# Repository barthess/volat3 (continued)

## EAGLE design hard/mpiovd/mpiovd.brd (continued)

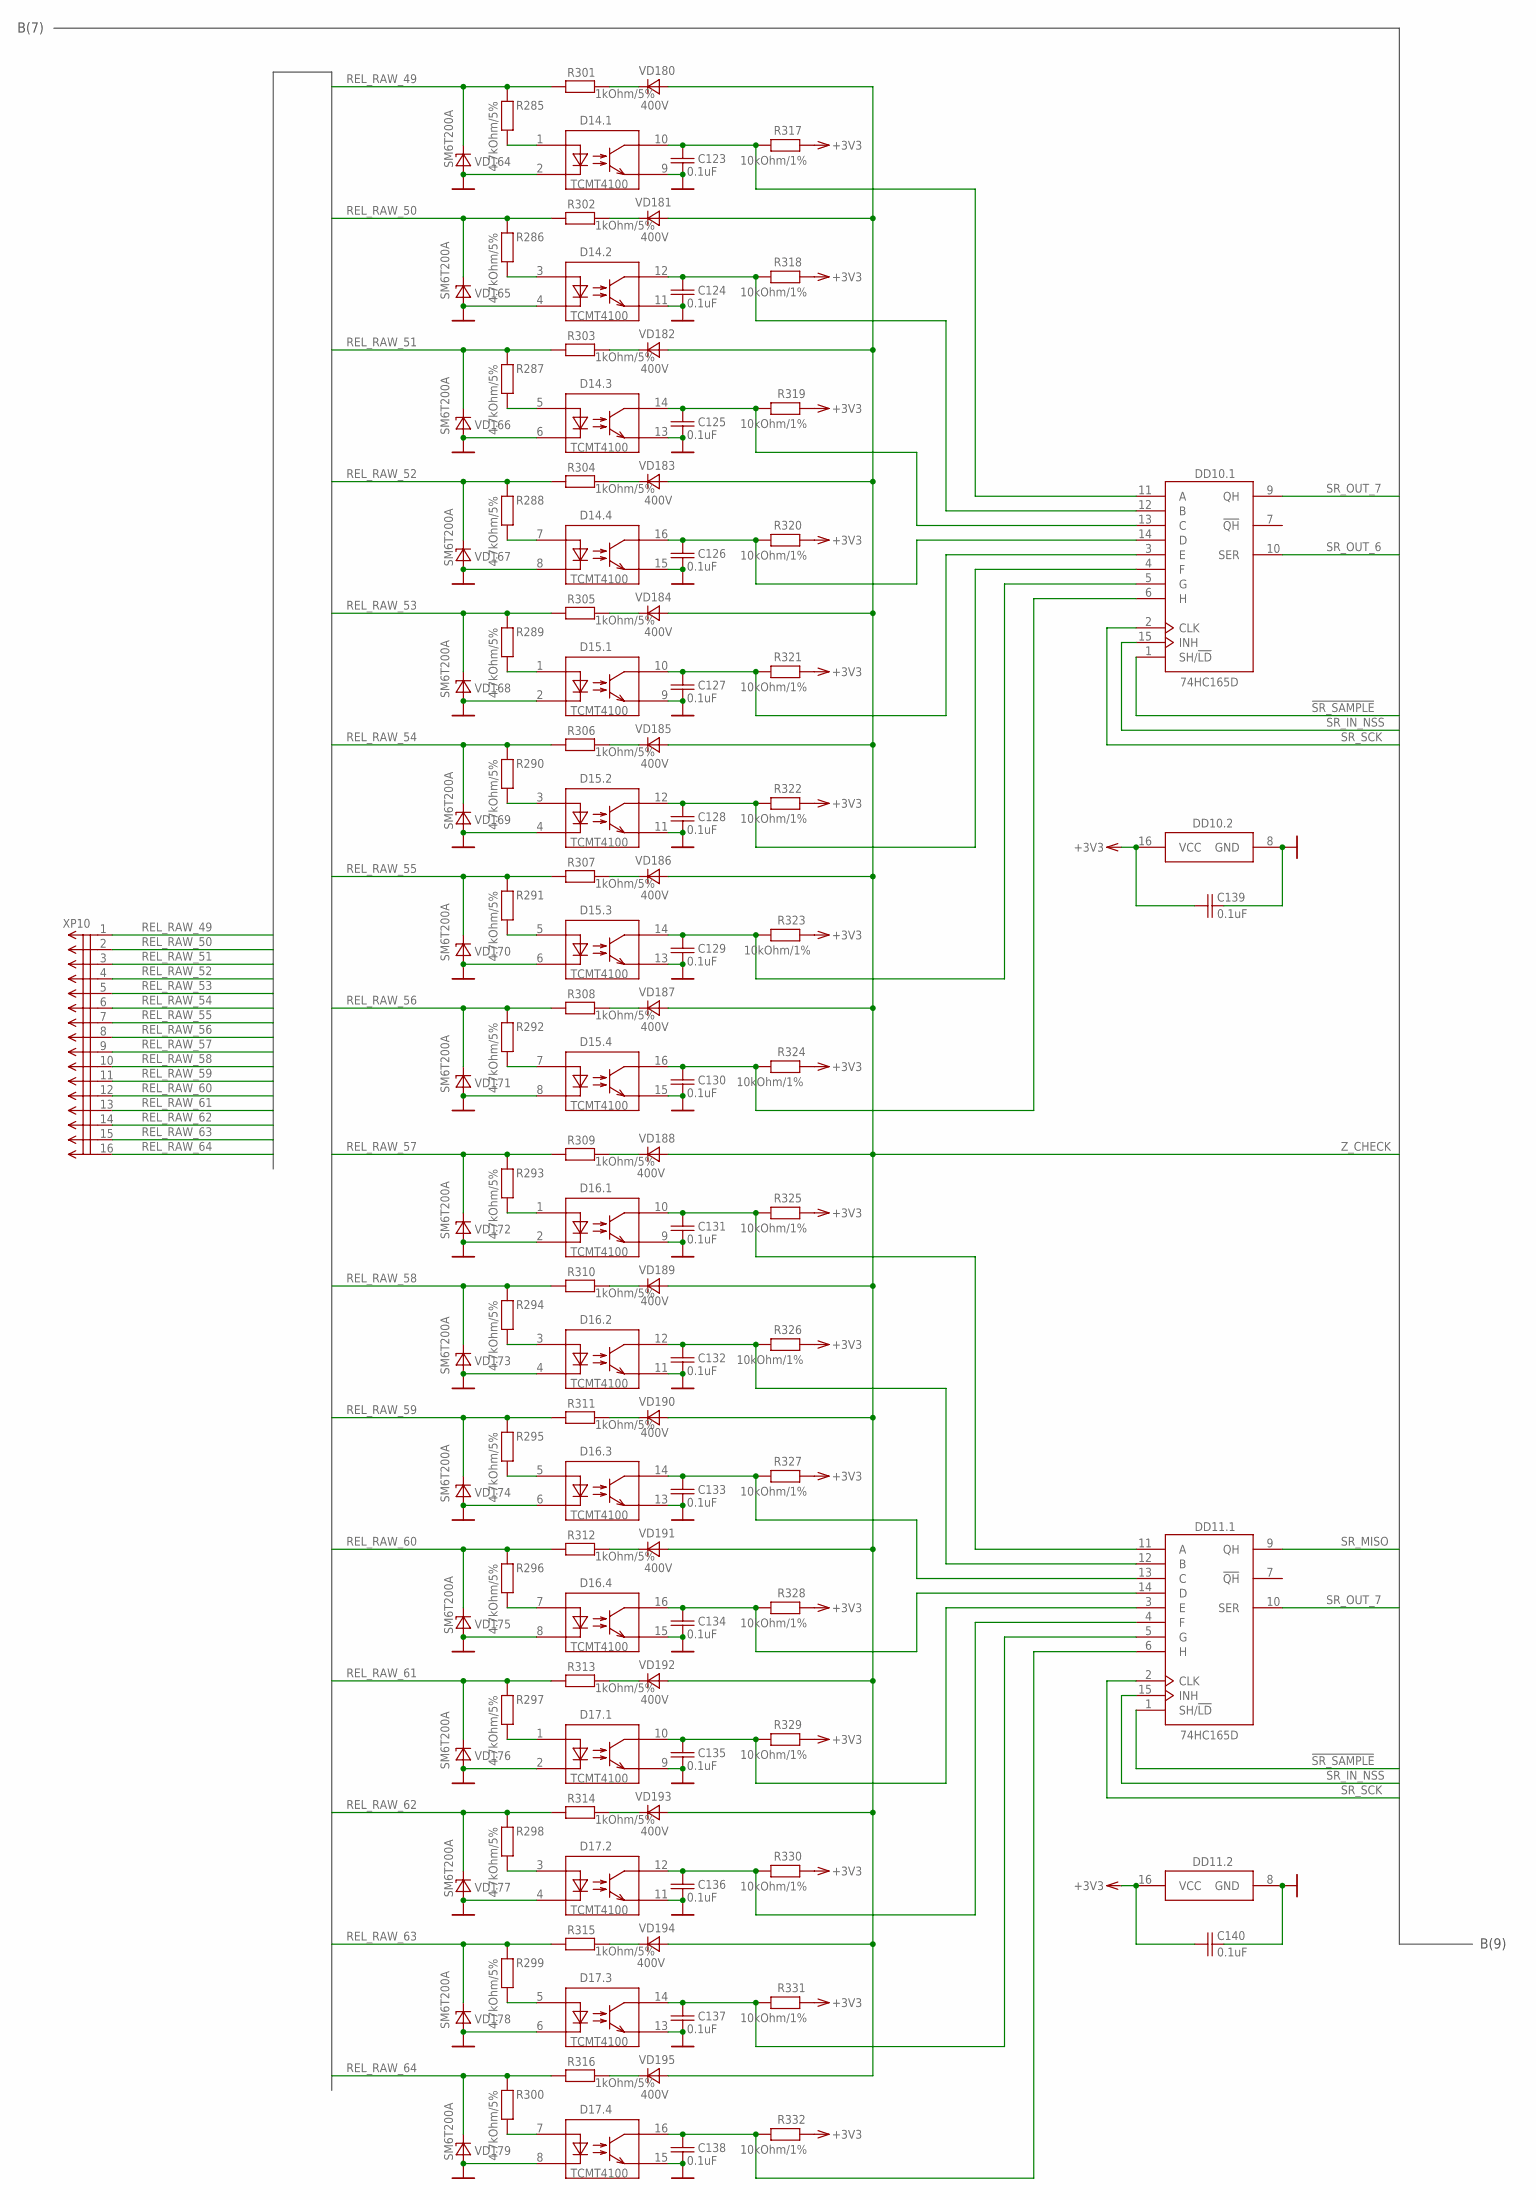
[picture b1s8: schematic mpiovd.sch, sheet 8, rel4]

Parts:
C123, C124, C125, C126, C127, C128, C129, C130, C131, C132, C133, C134, C135, C136, C137, C138, C139, C140: 0.1uF; C0603; PARTNO C0603C104K5RACTU
D14, D15, D16, D17: TCMT4100; SO16; PARTNO TCMT4100
DD10, DD11: 74HC165D; SO16; PARTNO IN74HC165AD
R285, R286, R287, R288, R289, R290, R291, R292, R293, R294, R295, R296, R297, R298, R299, R300: 4.7kOhm/5%; R1206; PARTNO RC1206JR-074K7L
R301, R302, R303, R304, R305, R306, R307, R308, R309, R310, R311, R312, R313, R314, R315, R316: 1kOhm/5%; R2512; PARTNO RC2512JK-071KL
R317, R318, R319, R320, R321, R322, R323, R324, R325, R326, R327, R328, R329, R330, R331, R332: 10kOhm/1%; R0603; PARTNO RC0603FR-1010KL
VD164, VD165, VD166, VD167, VD168, VD169, VD170, VD171, VD172, VD173, VD174, VD175, VD176, VD177, VD178, VD179: SM6T200A; SMB; PARTNO SM6T200A
VD180, VD181, VD182, VD183, VD184, VD185, VD186, VD187, VD188, VD189, VD190, VD191, VD192, VD193, VD194, VD195: 400V; SMA; PARTNO S1G-E3/61T
XP10: MOLEX-90130-16; PARTNO 90130-1216

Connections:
!SR_SAMPLE: DD10.1 (SH/!LD), DD11.1 (SH/!LD); also elsewhere on the board
+3V3: C139.1, C140.1, DD10.16 (VCC), DD11.16 (VCC), R317.1, R318.1, R319.1, R320.1, R321.1, R322.1, R323.1, R324.1, R325.1, R326.1, R327.1, R328.1, R329.1, R330.1, R331.1, R332.1; also elsewhere on the board
DISCRETE_49: C123.1, D14.10 (TC), DD10.11 (A), R317.2
DISCRETE_50: C124.1, D14.12 (TC), DD10.12 (B), R318.2
DISCRETE_51: C125.1, D14.14 (TC), DD10.13 (C), R319.2
DISCRETE_52: C126.1, D14.16 (TC), DD10.14 (D), R320.2
DISCRETE_53: C127.1, D15.10 (TC), DD10.3 (E), R321.2
DISCRETE_54: C128.1, D15.12 (TC), DD10.4 (F), R322.2
DISCRETE_55: C129.1, D15.14 (TC), DD10.5 (G), R323.2
DISCRETE_56: C130.1, D15.16 (TC), DD10.6 (H), R324.2
DISCRETE_57: C131.1, D16.10 (TC), DD11.11 (A), R325.2
DISCRETE_58: C132.1, D16.12 (TC), DD11.12 (B), R326.2
DISCRETE_59: C133.1, D16.14 (TC), DD11.13 (C), R327.2
DISCRETE_60: C134.1, D16.16 (TC), DD11.14 (D), R328.2
DISCRETE_61: C135.1, D17.10 (TC), DD11.3 (E), R329.2
DISCRETE_62: C136.1, D17.12 (TC), DD11.4 (F), R330.2
DISCRETE_63: C137.1, D17.14 (TC), DD11.5 (G), R331.2
DISCRETE_64: C138.1, D17.16 (TC), DD11.6 (H), R332.2
GND: C123.2, C124.2, C125.2, C126.2, C127.2, C128.2, C129.2, C130.2, C131.2, C132.2, C133.2, C134.2, C135.2, C136.2, C137.2, C138.2, C139.2, C140.2, D14.2 (DC), D14.4 (DC), D14.6 (DC), D14.8 (DC), D14.9 (TE), D14.11 (TE), D14.13 (TE), D14.15 (TE), D15.2 (DC), D15.4 (DC), D15.6 (DC), D15.8 (DC), D15.9 (TE), D15.11 (TE), D15.13 (TE), D15.15 (TE), D16.2 (DC), D16.4 (DC), D16.6 (DC), D16.8 (DC), D16.9 (TE), D16.11 (TE), D16.13 (TE), D16.15 (TE), D17.2 (DC), D17.4 (DC), D17.6 (DC), D17.8 (DC), D17.9 (TE), D17.11 (TE), D17.13 (TE), D17.15 (TE), DD10.8 (GND), DD11.8 (GND), VD164.A, VD165.A, VD166.A, VD167.A, VD168.A, VD169.A, VD170.A, VD171.A, VD172.A, VD173.A, VD174.A, VD175.A, VD176.A, VD177.A, VD178.A, VD179.A; also elsewhere on the board
unnamed: R301.2, VD180.C
unnamed: R302.2, VD181.C
unnamed: R303.2, VD182.C
unnamed: R304.2, VD183.C
unnamed: R305.2, VD184.C
unnamed: R306.2, VD185.C
unnamed: R307.2, VD186.C
unnamed: R308.2, VD187.C
unnamed: R309.2, VD188.C
unnamed: R310.2, VD189.C
unnamed: R311.2, VD190.C
unnamed: R312.2, VD191.C
unnamed: R313.2, VD192.C
unnamed: R314.2, VD193.C
unnamed: R315.2, VD194.C
unnamed: R316.2, VD195.C
unnamed: D14.1 (DA), R285.2
unnamed: D14.3 (DA), R286.2
unnamed: D14.5 (DA), R287.2
unnamed: D14.7 (DA), R288.2
unnamed: D15.1 (DA), R289.2
unnamed: D15.3 (DA), R290.2
unnamed: D15.5 (DA), R291.2
unnamed: D15.7 (DA), R292.2
unnamed: D16.1 (DA), R293.2
unnamed: D16.3 (DA), R294.2
unnamed: D16.5 (DA), R295.2
unnamed: D16.7 (DA), R296.2
unnamed: D17.1 (DA), R297.2
unnamed: D17.3 (DA), R298.2
unnamed: D17.5 (DA), R299.2
unnamed: D17.7 (DA), R300.2
REL_RAW_49: R285.1, R301.1, VD164.C, XP10.1
REL_RAW_50: R286.1, R302.1, VD165.C, XP10.2
REL_RAW_51: R287.1, R303.1, VD166.C, XP10.3
REL_RAW_52: R288.1, R304.1, VD167.C, XP10.4
REL_RAW_53: R289.1, R305.1, VD168.C, XP10.5
REL_RAW_54: R290.1, R306.1, VD169.C, XP10.6
REL_RAW_55: R291.1, R307.1, VD170.C, XP10.7
REL_RAW_56: R292.1, R308.1, VD171.C, XP10.8
REL_RAW_57: R293.1, R309.1, VD172.C, XP10.9
REL_RAW_58: R294.1, R310.1, VD173.C, XP10.10
REL_RAW_59: R295.1, R311.1, VD174.C, XP10.11
REL_RAW_60: R296.1, R312.1, VD175.C, XP10.12
REL_RAW_61: R297.1, R313.1, VD176.C, XP10.13
REL_RAW_62: R298.1, R314.1, VD177.C, XP10.14
REL_RAW_63: R299.1, R315.1, VD178.C, XP10.15
REL_RAW_64: R300.1, R316.1, VD179.C, XP10.16
SR_IN_NSS: DD10.15 (INH), DD11.15 (INH); also elsewhere on the board
SR_MISO: DD11.9 (QH); also elsewhere on the board
SR_OUT_6: DD10.10 (SER); also elsewhere on the board
SR_OUT_7: DD10.9 (QH), DD11.10 (SER)
SR_SCK: DD10.2 (CLK), DD11.2 (CLK); also elsewhere on the board
Z_CHECK: VD180.A, VD181.A, VD182.A, VD183.A, VD184.A, VD185.A, VD186.A, VD187.A, VD188.A, VD189.A, VD190.A, VD191.A, VD192.A, VD193.A, VD194.A, VD195.A; also elsewhere on the board

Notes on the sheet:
B(9)
B(7)

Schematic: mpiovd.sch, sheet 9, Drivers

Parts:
C141: 0.1uF; C0603; PARTNO C0603C104K5RACTU
D18, D19: TCMT4100; SO16; PARTNO TCMT4100
D20, D21, D22, D23, D24, D25, D26, D27: AUIPS7111S; TO252-5-11; PARTNO AUIPS7111S
DD12: 74HC595D; SO16; PARTNO IN74HC595AD
R333: 10kOhm/1%; R0603; PARTNO RC0603FR-1010KL
R334, R335, R336, R337, R338, R339, R340, R341: 100Ohm/5%; R0603; PARTNO ERJ3GEYJ101V
R342, R343, R344, R345, R346, R347, R348, R349, R350, R351, R352, R353, R354, R355, R356, R357: 1kOhm/5%; R0805; PARTNO ERJ6GEYJ102V
VD196, VD197, VD198, VD199, VD200, VD201, VD202, VD203, VD204, VD205, VD206, VD207, VD208, VD209, VD210, VD211: 100V; SOD323; PARTNO 1N4148WS-V-GS18
XP11: MOLEX-90130-34; PARTNO 90130-1234

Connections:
!SR_OUT_ENABLE: DD12.13 (!OE), R333.1; also elsewhere on the board
+3V3: C141.1, DD12.10 (!MR), DD12.16 (VCC), R333.2; also elsewhere on the board
GND: C141.2, D18.2 (DC), D18.4 (DC), D18.6 (DC), D18.8 (DC), D18.9 (TE), D18.11 (TE), D18.13 (TE), D18.15 (TE), D19.2 (DC), D19.4 (DC), D19.6 (DC), D19.8 (DC), D19.9 (TE), D19.11 (TE), D19.13 (TE), D19.15 (TE), DD12.8 (GND), R342.1, R343.1, R344.1, R345.1, R346.1, R347.1, R348.1, R349.1, VD196.A, VD197.A, VD198.A, VD199.A, VD200.A, VD201.A, VD202.A, VD203.A; also elsewhere on the board
unnamed: D27.1 (IN), R357.2
unnamed: D26.1 (IN), R356.2
unnamed: D25.1 (IN), R355.2
unnamed: D24.1 (IN), R354.2
unnamed: D23.1 (IN), R353.2
unnamed: D22.1 (IN), R352.2
unnamed: D21.1 (IN), R351.2
unnamed: D20.1 (IN), R350.2
unnamed: D19.7 (DA), R341.1
unnamed: D18.10 (TC), R350.1, VD196.C
unnamed: D18.12 (TC), R351.1, VD197.C
unnamed: D18.14 (TC), R352.1, VD198.C
unnamed: D18.16 (TC), R353.1, VD199.C
unnamed: D19.10 (TC), R354.1, VD200.C
unnamed: D19.12 (TC), R355.1, VD201.C
unnamed: D19.14 (TC), R356.1, VD202.C
unnamed: D19.16 (TC), R357.1, VD203.C
unnamed: D19.5 (DA), R340.1
unnamed: D19.3 (DA), R339.1
unnamed: D19.1 (DA), R338.1
unnamed: D18.7 (DA), R337.1
unnamed: D18.5 (DA), R336.1
unnamed: D18.3 (DA), R335.1
unnamed: D18.1 (DA), R334.1
unnamed: DD12.15 (QA), R334.2
unnamed: D20.2 (IFB), VD204.A
unnamed: D21.2 (IFB), VD205.A
unnamed: D22.2 (IFB), VD206.A
unnamed: D23.2 (IFB), VD207.A
unnamed: D24.2 (IFB), VD208.A
unnamed: D25.2 (IFB), VD209.A
unnamed: D26.2 (IFB), VD210.A
unnamed: D27.2 (IFB), VD211.A
unnamed: DD12.1 (QB), R335.2
unnamed: DD12.2 (QC), R336.2
unnamed: DD12.7 (QH), R341.2
unnamed: DD12.6 (QG), R340.2
unnamed: DD12.5 (QF), R339.2
unnamed: R342.2, VD204.C
unnamed: R343.2, VD205.C
unnamed: R344.2, VD206.C
unnamed: R345.2, VD207.C
unnamed: R346.2, VD208.C
unnamed: DD12.3 (QD), R337.2
unnamed: DD12.4 (QE), R338.2
unnamed: R347.2, VD209.C
unnamed: R348.2, VD210.C
unnamed: R349.2, VD211.C
OUT_DRV1: D20.4 (OUT1), D20.5 (OUT2), XP11.1, XP11.4
OUT_DRV2: D21.4 (OUT1), D21.5 (OUT2), XP11.5, XP11.8
OUT_DRV3: D22.4 (OUT1), D22.5 (OUT2), XP11.9, XP11.12
OUT_DRV4: D23.4 (OUT1), D23.5 (OUT2), XP11.13, XP11.16
OUT_DRV5: D24.4 (OUT1), D24.5 (OUT2), XP11.17, XP11.20
OUT_DRV6: D25.4 (OUT1), D25.5 (OUT2), XP11.21, XP11.24
OUT_DRV7: D26.4 (OUT1), D26.5 (OUT2), XP11.25, XP11.28
OUT_DRV8: D27.4 (OUT1), D27.5 (OUT2), XP11.29, XP11.32
SR_MOSI: DD12.14 (SER); also elsewhere on the board
SR_OUT_NSS: DD12.12 (STCP); also elsewhere on the board
SR_SCK: DD12.11 (SHCP); also elsewhere on the board
VCC_DRV1: D20.TAB (VCC), XP11.2, XP11.3
VCC_DRV2: D21.TAB (VCC), XP11.6, XP11.7
VCC_DRV3: D22.TAB (VCC), XP11.10, XP11.11
VCC_DRV4: D23.TAB (VCC), XP11.14, XP11.15
VCC_DRV5: D24.TAB (VCC), XP11.18, XP11.19
VCC_DRV6: D25.TAB (VCC), XP11.22, XP11.23
VCC_DRV7: D26.TAB (VCC), XP11.26, XP11.27
VCC_DRV8: D27.TAB (VCC), XP11.30, XP11.31

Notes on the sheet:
B(8)

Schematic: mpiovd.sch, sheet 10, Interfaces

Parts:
C142, C143, C144, C145, C146, C147: 0.1uF; C0603; PARTNO C0603C104K5RACTU
DA15: USBUF01W6; SOTT323-6L; PARTNO USBUF01W6
DA16: SN65HVD232; SO08; PARTNO SN65HVD232D
DA17: ILX3232D; SO16; PARTNO ILX3232D
L4: EXC3BP; L0603; PARTNO EXC3BP121H
R358: 120Ohm/5%; R1206; PARTNO RC1206JR-07120RL
R359, R361: 10kOhm/1%; R0603; PARTNO RC0603FR-1010KL
R360: 36kOhm/5%; R0603; PARTNO ERJ3GEYJ363V
R362: 47kOhm/5%; R0603; PARTNO ERJ3GEYJ473V
R363, R364: 1kOhm/5%; R0805; PARTNO ERJ6GEYJ102V
VD212, VD213: SMBJ24CA; SMB-BIDIR; PARTNO SMBJ24CA
VD214: 3.3V; SOD80; PARTNO BZV55-C3V3
VT3, VT4: BC817-16SMD; SOT23-BEC; PARTNO BC817
XP12: MOLEX-90130-08; PARTNO 90130-1208
XP13: PLD_1X02; PARTNO 825433-2
XS1: USB-MINIB_(SOVOK-UGO); USB-MINIB; PARTNO MUBS1-05SN2
Z42, Z43, Z44, Z45, Z46, Z47, Z48, Z49, Z50: NFE31PT; NFE31; PARTNO NFE31PT152Z1E9

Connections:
+3V3: C142.2, DA16.3 (VCC), R362.2, VT3.C; also elsewhere on the board
+3V3_DIRT: C144.1, DA17.16 (VCC); also elsewhere on the board
+5V_USB: L4.2, R359.2, R361.2, VT3.B; also elsewhere on the board
CANH: DA16.7 (CANH), XP12.2, XP13.1
CANL: DA16.6 (CANL), R358.2, XP12.1
CAN_RX: Z47.3; also elsewhere on the board
CAN_TX: Z50.3; also elsewhere on the board
D+: XS1.D+ (3), Z42.3
D-: XS1.D- (2), Z43.3
FROM_RS232: VD213.A2, XP12.3, Z46.1
GND: C142.1, C143.2, C144.2, C145.2, DA15.2 (GND), DA16.2 (GND), DA17.15 (GND), R360.1, VD212.A1, VD213.A1, VD214.A, VT4.E, XS1.GND (5), Z42.2, Z43.2, Z44.2, Z45.2, Z46.2, Z47.2, Z48.2, Z49.2, Z50.2; also elsewhere on the board
unnamed: R358.1, XP13.2
unnamed: R362.1, R364.1, VT4.B
unnamed: R359.1, R360.2, VT4.C
unnamed: VT3.E, Z44.3
unnamed: R361.1, R363.1, VD214.C
unnamed: L4.1, XS1.VBUS (1)
unnamed: C143.1, DA17.2 (V+)
unnamed: C145.1, DA17.6 (V-)
unnamed: DA17.8 (R2IN), Z46.3
unnamed: DA17.7 (T2OUT), Z45.3
unnamed: C146.2, DA17.3 (C1-)
unnamed: C146.1, DA17.1 (C1+)
unnamed: C147.1, DA17.4 (C2+)
unnamed: C147.2, DA17.5 (C2-)
unnamed: DA16.1 (TXD), Z50.1
unnamed: DA16.4 (RXD), Z47.1
unnamed: DA15.5 (3.3V), Z44.1
unnamed: R364.2, Z49.1
unnamed: R363.2, Z48.1
unnamed: DA15.4 (D3), Z43.1
unnamed: DA15.6 (D4), Z42.1
TO_RS232: VD212.A2, XP12.4, Z45.1
USART_FROM_MCU: DA17.10 (T2IN); also elsewhere on the board
USART_TO_MCU: DA17.9 (R2OUT); also elsewhere on the board
USBDM: DA15.3 (D2); also elsewhere on the board
USBDP: DA15.1 (D1); also elsewhere on the board
USB_DISCOVERY: Z49.3; also elsewhere on the board
USB_PRESENT: Z48.3; also elsewhere on the board

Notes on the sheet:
C(3)

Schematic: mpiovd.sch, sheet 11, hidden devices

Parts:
JP1, JP2, JP3, JP4, JP5, JP6, JP7, JP8: STAND-OFF-M4
JP9, JP10: STAND-OFF-M3

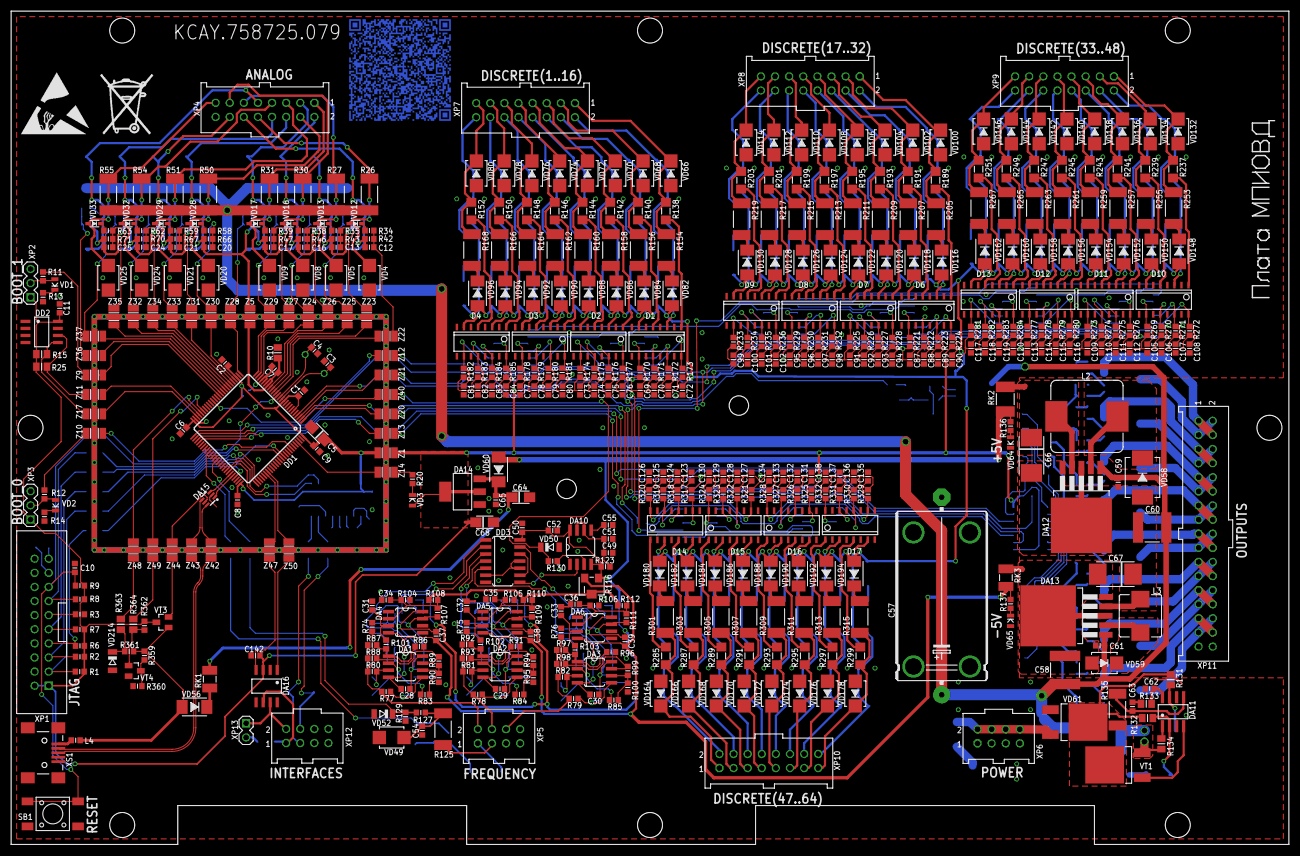
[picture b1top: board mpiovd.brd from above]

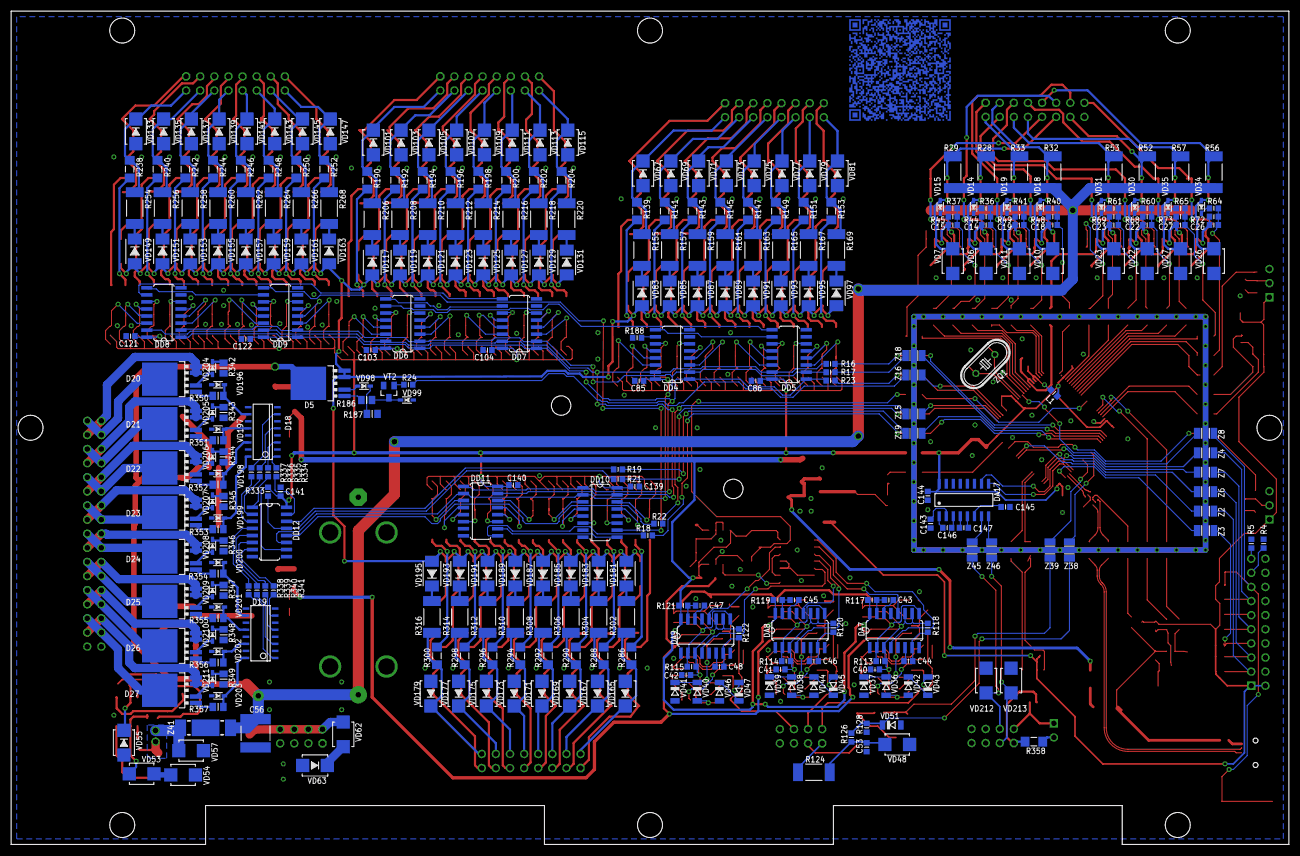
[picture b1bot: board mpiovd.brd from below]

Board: 2 copper layers, 230.0 x 150.0 mm, 871 parts (335 on the bottom side), 591 nets.

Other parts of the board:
U$1: STATIC_12
U$2: NOT_RECYCLE_12
U$3: QR

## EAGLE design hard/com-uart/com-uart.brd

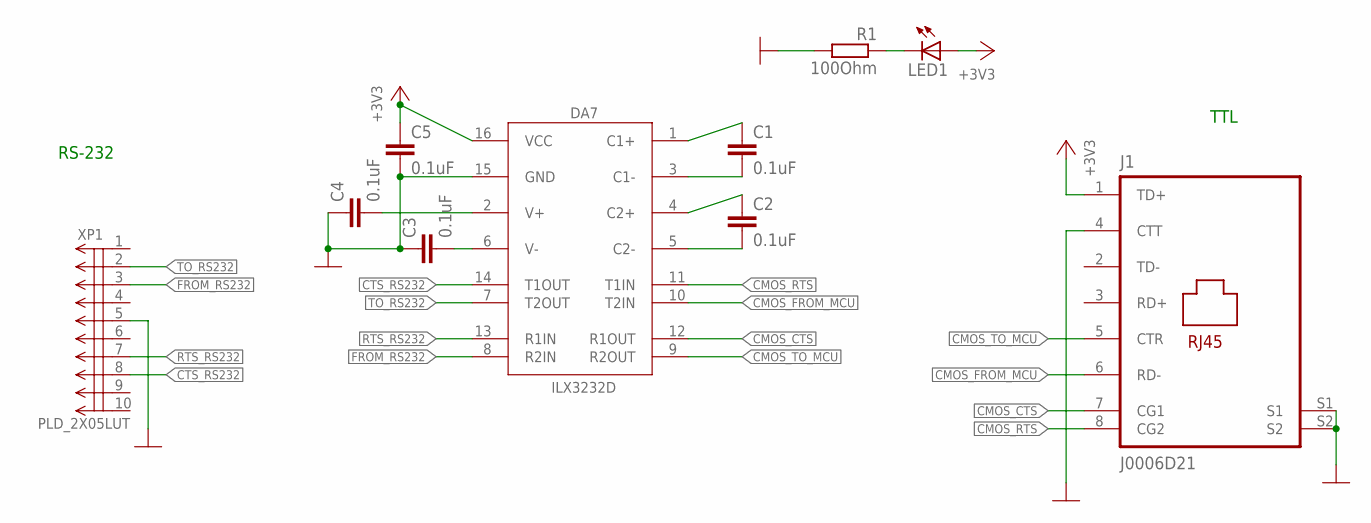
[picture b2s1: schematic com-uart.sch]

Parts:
C1, C2, C3, C4, C5: 0.1uF; 0805
DA7: ILX3232D; SO16; PARTNO ILX3232D
J1: J0006D21; J0-C/D/E
LED1: LED3MM
R1: 100Ohm; 0805
XP1: PLD_2X05LUT; PLD_2X05_LUT

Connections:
+3V3: C5.1, DA7.16 (VCC), J1.1 (TD+), LED1.A
CMOS_CTS: DA7.12 (R1OUT), J1.7 (CG1)
CMOS_FROM_MCU: DA7.10 (T2IN), J1.6 (RD-)
CMOS_RTS: DA7.11 (T1IN), J1.8 (CG2)
CMOS_TO_MCU: DA7.9 (R2OUT), J1.5 (CTR)
CTS_RS232: DA7.14 (T1OUT), XP1.8
FROM_RS232: DA7.8 (R2IN), XP1.3
GND: C3.1, C4.1, C5.2, DA7.15 (GND), J1.4 (CTT), J1.S1, J1.S2, R1.2, XP1.5
unnamed: LED1.K (C), R1.1
unnamed: C4.2, DA7.2 (V+)
unnamed: C3.2, DA7.6 (V-)
unnamed: C1.2, DA7.3 (C1-)
unnamed: C1.1, DA7.1 (C1+)
unnamed: C2.1, DA7.4 (C2+)
unnamed: C2.2, DA7.5 (C2-)
RTS_RS232: DA7.13 (R1IN), XP1.7
TO_RS232: DA7.7 (T2OUT), XP1.2

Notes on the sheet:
TTL
RS-232

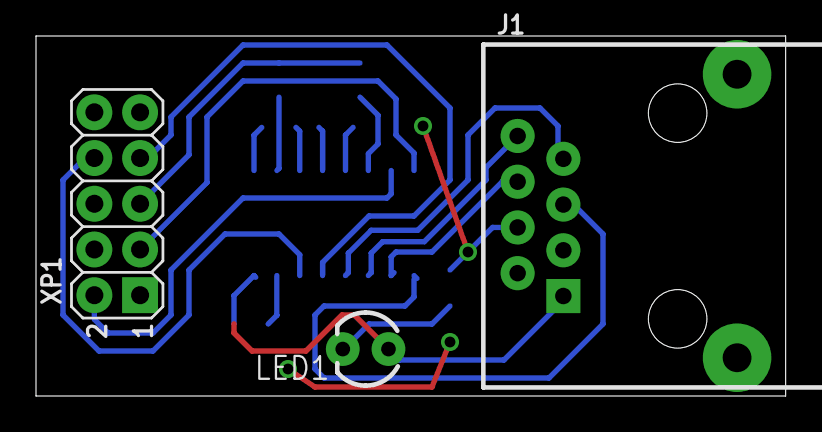
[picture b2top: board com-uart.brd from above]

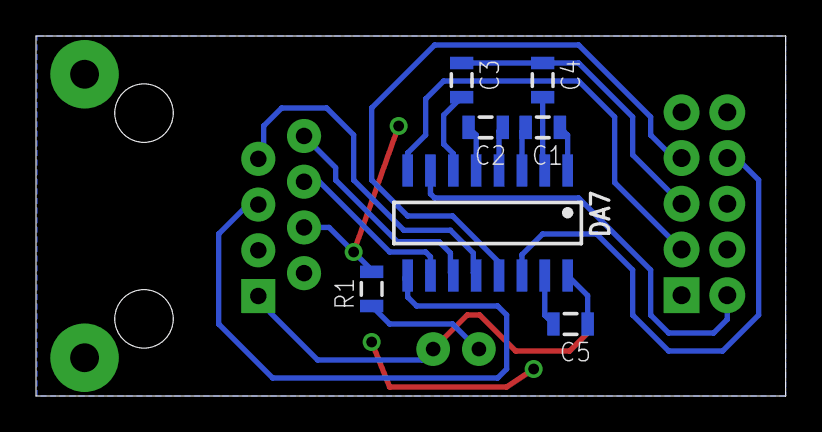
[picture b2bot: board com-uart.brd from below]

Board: 2 copper layers, 41.6 x 20.0 mm, 10 parts (7 on the bottom side), 17 nets.

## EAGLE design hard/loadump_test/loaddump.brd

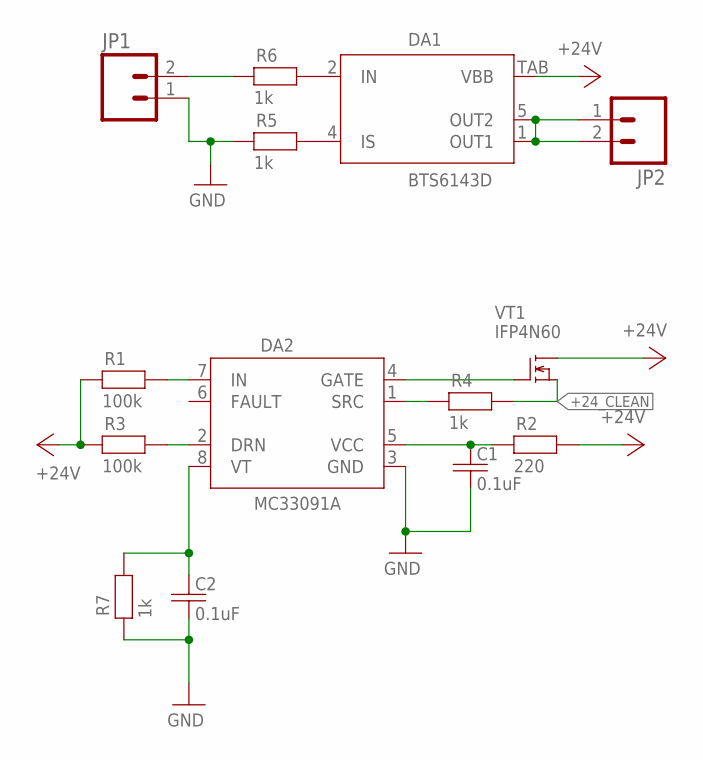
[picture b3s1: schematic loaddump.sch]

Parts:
C1, C2: 0.1uF; C0805
DA1: BTS6143D; TO252-5-11
DA2: MC33091A; SO08
JP1, JP2: M02PTH3; 1X02_LONGPADS
R1, R3: 100k; R0805
R2: 220; 0922/22
R4, R5, R6, R7: 1k; R0805
VT1: IFP4N60; TO220

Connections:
+24V: DA1.TAB (VBB), R1.1, R2.2, R3.1, VT1.2 (D)
+24_CLEAN: R4.2, VT1.3 (S)
GND: C1.2, C2.2, DA2.3 (GND), JP1.1, R5.1, R7.1
unnamed: DA2.7 (IN), R1.2
unnamed: DA2.4 (GATE), VT1.1 (G)
unnamed: C1.1, DA2.5 (VCC), R2.1
unnamed: DA2.2 (DRN), R3.2
unnamed: DA2.1 (SRC), R4.1
unnamed: DA1.1 (OUT1), DA1.5 (OUT2), JP2.1, JP2.2
unnamed: DA1.4 (IS), R5.2
unnamed: DA1.2 (IN), R6.2
unnamed: JP1.2, R6.1
unnamed: C2.1, DA2.8 (VT), R7.2

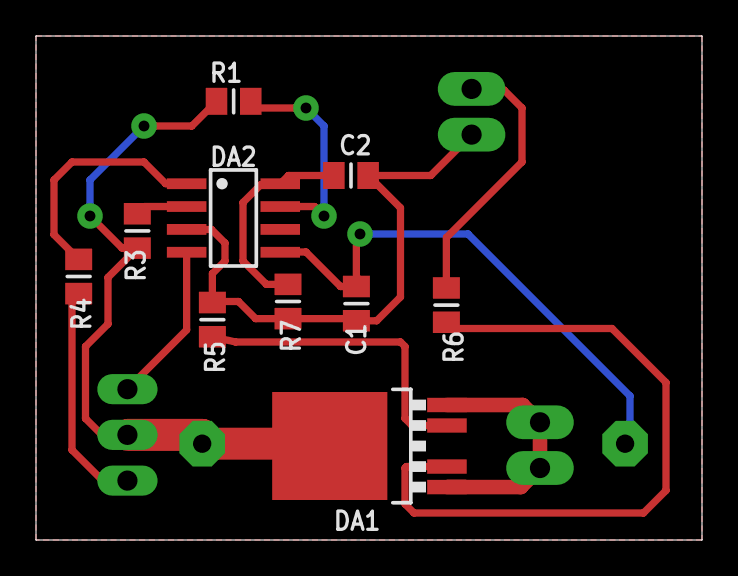
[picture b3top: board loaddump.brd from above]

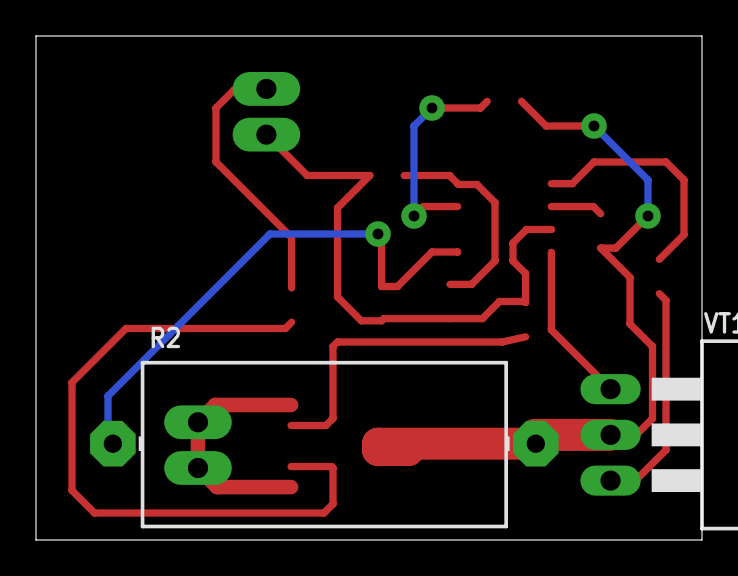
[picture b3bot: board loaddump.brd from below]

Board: 2 copper layers, 37.0 x 28.0 mm, 14 parts (2 on the bottom side), 13 nets.

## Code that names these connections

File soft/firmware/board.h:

/*
    ChibiOS/RT - Copyright (C) 2006,2007,2008,2009,2010,
                 2011,2012 Giovanni Di Sirio.

    This file is part of ChibiOS/RT.

    ChibiOS/RT is free software; you can redistribute it and/or modify
    it under the terms of the GNU General Public License as published by
    the Free Software Foundation; either version 3 of the License, or
    (at your option) any later version.

    ChibiOS/RT is distributed in the hope that it will be useful,
    but WITHOUT ANY WARRANTY; without even the implied warranty of
    MERCHANTABILITY or FITNESS FOR A PARTICULAR PURPOSE.  See the
    GNU General Public License for more details.

    You should have received a copy of the GNU General Public License
    along with this program.  If not, see <http://www.gnu.org/licenses/>.
*/

#ifndef _BOARD_H_
#define _BOARD_H_

/*
 * Setup for the MPIOVD board.
 */

/*
 * Board identifier.
 */
#define BOARD_MPIOVD
#define BOARD_NAME              "MPIOVD rev.1 board"

/*
 * Board frequencies.
 */
#define STM32_LSECLK            0
#define STM32_HSECLK            4000000

/*
 * MCU type, supported types are defined in ./os/hal/platforms/hal_lld.h.
 */
#define STM32F10X_HD

/*
 * IO pins assignments.
 */

#define GPIOB_BOOT_1            2
#define GPIOB_SR_IN_NSS         12

#define GPIOC_FREQUENCY         6
#define GPIOC_USB_DISC

#define GPIOE_LED               0
#define GPIOE_SR_OUT_NSS        3
#define GPIOE_SR_SAMPLE         4
#define GPIOE_Z_CHECK           5
#define GPIOE_SPEEDOMETER       8
#define GPIOE_USB_DISCOVERY     14
#define GPIOE_USB_PRESENT       15

#define GPIOD_CAN_RX            0
#define GPIOD_CAN_TX            1
#define GPIOD_TACHOMETER        12

/*
 * I/O ports initial setup, this configuration is established soon after reset
 * in the initialization code.
 *
 * The digits have the following meaning:
 *   0 - Analog input.
 *   1 - Push Pull output 10MHz.
 *   2 - Push Pull output 2MHz.
 *   3 - Push Pull output 50MHz.
 *   4 - Digital input.
 *   5 - Open Drain output 10MHz.
 *   6 - Open Drain output 2MHz.
 *   7 - Open Drain output 50MHz.
 *   8 - Digital input with PullUp or PullDown resistor depending on ODR.
 *   9 - Alternate Push Pull output 10MHz.
 *   A - Alternate Push Pull output 2MHz.
 *   B - Alternate Push Pull output 50MHz.
 *   C - Reserved.
 *   D - Alternate Open Drain output 10MHz.
 *   E - Alternate Open Drain output 2MHz.
 *   F - Alternate Open Drain output 50MHz.
 * Please refer to the STM32 Reference Manual for details.
 */

/*
 * Port A setup.
 * Everything input with pull-up except:
 * PA0..PA7 - analog input.
 */
#define VAL_GPIOACRL            0x00000000      /*  PA7...PA0 */
#define VAL_GPIOACRH            0x888884A8      /* PA15...PA8 */
#define VAL_GPIOAODR            0xFFFFFFFF

/*
 * Port B setup.
 * Everything input with pull-up except:
 * PB0,1 - Analog input.
 * PB10,11 - I2C.
 * PB12 - serial input NSS
 * PB13 - serial clock
 * PB14 - serial input MISO
 * PB15 - serial input MOSI
 */
#define VAL_GPIOBCRL            0xEE888800      /*  PB7...PB0 */
#define VAL_GPIOBCRH            0xA4A2EE88      /* PB15...PB8 */
#define VAL_GPIOBODR            0x0

/*
 * Port C setup.
 * Everything input with pull-up except:
 * PC0..PC5 - analog input
 * PC6 - frequency meter
 *
 */
#define VAL_GPIOCCRL            0x88400000      /*  PC7...PC0 */
#define VAL_GPIOCCRH            0x88863388      /* PC15...PC8 */
#define VAL_GPIOCODR            0xFFFFFFFF

/*
 * Port D setup.
 * Everything input with pull-up except:
 * PD0  - CAN RX.
 * PD1  - CAN TX.
 * PD12 - tachometer
 */
#define VAL_GPIODCRL            0x888888A4      /*  PD7...PD0 */
#define VAL_GPIODCRH            0x88848888      /* PD15...PD8 */
#define VAL_GPIODODR            0xFFFFFFFF

/*
 * Port E setup.
 * Everything input with pull-up except:
 * PE0 - LED
 * PE2 - serial out ENABLE
 * PE3 - serial out NSS
 * PE4 - serial SAMPLE
 * PE5 - serial Z_CHECK_TOGGLE
 * PE9 - spedometer input
 * PE14 - usb discovery
 * PE15 - usb present
 */
#define VAL_GPIOECRL            0x88222286      /*  PE7...PE0 */
#define VAL_GPIOECRH            0x42888848      /* PE15...PE8 */
#define VAL_GPIOEODR            0xFFFFFFFF

/*
 * Port F setup. Stub
 */
#define VAL_GPIOFCRL            0x88888888      /*  PE7...PE0 */
#define VAL_GPIOFCRH            0x88888888      /* PE15...PE8 */
#define VAL_GPIOFODR            0xFFFFFFFF

/*
 * Port G setup. Stub
 */
#define VAL_GPIOGCRL            0x88888888      /*  PE7...PE0 */
#define VAL_GPIOGCRH            0x88888888      /* PE15...PE8 */
#define VAL_GPIOGODR            0xFFFFFFFF

/*
 * USB bus activation macro, required by the USB driver.
 */
#define usb_lld_connect_bus(usbp) palClearPad(GPIOE, GPIOE_USB_DISCOVERY)

/*
 * USB bus de-activation macro, required by the USB driver.
 */
#define usb_lld_disconnect_bus(usbp) palSetPad(GPIOE, GPIOE_USB_DISCOVERY)

#if !defined(_FROM_ASM_)
#ifdef __cplusplus
extern "C" {
#endif
  void boardInit(void);
#ifdef __cplusplus
}
#endif
#endif /* _FROM_ASM_ */

#endif /* _BOARD_H_ */

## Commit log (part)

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2012-05-18 added some common images
2012-05-18 improvemetns in pasport
2012-05-18 switched on paper format field
2012-05-18 n contr
2012-05-18 fixed molex connector
2012-05-21 modified to changes in eskdx
2012-05-21 n contr fixes
2012-05-21 added print job for soldering map
2012-05-22 dimension lines added
2012-05-22 path reorganization
2012-05-22 path reorganization 2
2012-05-22 path reorganization 3
2012-05-22 path reorganization 4
2012-05-22 added some symbols
2012-05-22 added job for generation gerbers in metric system
2012-05-23 ncontr
2012-05-28 message definition updated
2012-05-28 file renamed
2012-05-28 renamed uvvu to mpiovd
2012-05-28 source compiled successfully
2012-05-29 usb via ACM work on demo board with 8MHz crystall
2012-05-30 fixed silkscreen after ncontr
2012-05-30 mavlink data parsing ready
2012-05-30 it compiles and works, but very buggy
2012-05-31 data sending works
2012-05-31 data acquiring and transmission done
2012-05-31 nop"
2012-05-31 eeprom and microrl merged
2012-06-01 removed unnecessary localconfig.py
2012-06-01 udp sending added
2012-06-01 parameters sending done
2012-06-04 switch to submoduled microrl
2012-06-04 added serial proxy process
2012-06-04 renamed main.py to cockpit.py, because now it is not main file
2012-06-04 updated config template
2012-06-04 link improvements
2012-06-05 plotter connected
2012-06-05 fixed issue with normal exiting
2012-06-05 added qtbased plotter
2012-06-05 rename files
2012-06-05 pyqtgraph added to gitignore
2012-06-06 tuner gui changes
2012-06-07 some changes in gui
2012-06-07 now link process pushes all decoded messages to queue
2012-06-07 fixed technical characteristics values
2012-06-08 fixed main ksau
2012-06-11 converted to utf8
2012-06-11 serial proxy now multithreaded
2012-06-11 cosmetic improvements of serial proxy
2012-06-12 code rewrittent to use mavutil
2012-06-12 tuner now can erceive parameters
2012-06-13 getting parameters works
2012-06-13 checkbox girid widget works
2012-06-14 checkboxes works
2012-06-14 rel class moved to separate module
2012-06-15 deleted unneeded files
2012-06-15 deleted unneded file
2012-06-15 structure reorganization
2012-06-15 cleaned imports of unexisting module dsp
2012-06-15 cleanups
2012-06-15 analog tuner begin
2012-06-20 fixed XP12 connector description
2012-06-22 fixed mistype
2012-06-25 some files renamed
2012-06-25 some changes in analog parameters
2012-06-28 chbios updated
2012-07-06 qtgraph dir added to ignore
2012-07-10 template fixed
2012-07-10 added filtering code
2012-07-10 renamed adc file
2012-07-10 adc code compile now
2012-07-10 configured ADC
2012-07-11 added template for discrete data reader
2012-07-13 added todo list for pacb
2012-07-13 removed FIR filtering code, added alpha-beta filter
2012-07-13 some migrations to new MCU
2012-07-16 UART, ADC, I2C, heartbeat works
2012-07-16 added SPI code. Not tested
2012-07-17 updated eeprom code
2012-07-18 todo updated
2012-07-19 todo update
2012-07-19 eeprom moved from i2c2 to i2c1 to solve DMA conflict
2012-07-19 SPI reading works
2012-07-20 discrete sensor normilize skeleton ready
2012-07-20 discrete improvements
2012-07-25 discrete reading ready but not tested
2012-07-25 dead code removed
2012-07-25 added firmware todo list
2012-07-25 added parameter BRD_revision
2012-07-25 parameters code revriting
2012-07-25 new parameter code compiles
2012-07-25 code cleanups
2012-07-25 code cleanups 2
2012-07-25 cosmetical improvements
2012-07-27 spi inputs improvements
2012-07-27 adc code begin
2012-07-27 reduced maximum analog filter lengt to 30
2012-07-31 ADC. Voltage measurements with compensation done
2012-08-03 fixes in eeprom parameters
2012-09-28 add some addtitional measurements
2012-09-28 rewrited code for ADC compensation
2012-09-28 file move
2012-09-28 removed unneeded parameters (compensation coefficients)
2012-10-01 added code to prevent overflow of resistance value
2012-10-01 added tachometer handling code
2012-10-01 now ADC samples ignored during sampling hiZ discrete inputs
2012-10-01 now ADC samples ignored during sampling hiZ discrete inputs. FIXED
2012-10-03 added parameter CLI
2012-10-03 parameters from shell works
2012-10-04 migrated to separate chibios source dir
2012-10-04 usb shell starts from thread manager
2012-10-04 added templates for CAN
2012-10-04 added untested code for CAN
2012-10-05 automatic sewitching between CAN and USB works
2012-10-08 sending data over CAN works
2012-10-17 added command to show data from sensors in console
2012-10-17 added console tuner on mavlink serial port
2012-10-18 added some interpolation functions
2012-10-19 added ability to set period of sending telemetry
2012-10-19 start of optimization
2012-10-19 block of pressure meters optimized
2012-10-19 battery indicator optimized
2012-10-19 fuel indicators optimized
2012-10-19 legs drawing optimized
2012-10-19 symbol grid optimized
2012-10-19 updated STOP symbol with black opaque background
2012-10-19 updated Makefile for pictures
2012-10-22 added point at 120 celsius for temperature sensor
2012-10-22 added particle system just for lulz
2012-10-22 changes in messagin system
2012-10-22 template of config file removed
2012-10-22 remapping via config started
2012-10-23 code saving data to eeprom started
2012-10-24 added new eeprom lib as submodule
2012-10-24 integrated fresh eeprom module
2012-10-24 removed dead code
2012-10-24 trip storage improvements. Works incorrectly
2012-10-25 updated todo for PCB
2012-10-26 add some new definitions to protocol xml file
2012-10-26 revrited shell api
2012-10-29 fixed comment in mavlink message definition
2012-10-29 storage cli done
2012-10-29 some fixes in telemetry HUD
2012-10-29 trip/uptime CLI finalized and tested
2012-10-30 added config ability for analog sensors map
2012-10-31 tiers block ready
2012-10-31 tiers and legs blocks ready and tested
2012-10-31 added loader for flashing over uart
2012-10-31 added storing to eeprom of default parameters in very first run
2012-11-07 deleted submodules
2012-11-07 deleteing submodules
2012-11-07 firmware renamed to mpiovd
2012-11-07 miragted to new directory structure
2012-11-07 added sources of bnap
2012-11-07 bnap compiles now
2012-11-08 face improvements
2012-11-08 added backup of bnap with display
2012-11-08 added template
2012-11-09 code reorganization
2012-11-09 sychronization between gps, heartbeat and DM thread works
2012-11-10 event based packer works
2012-11-10 generator for packer done
2012-11-10 added gps message understanded by QGC
2012-11-12 i2c and DS1338 works
2012-11-12 old junk directory renamed
2012-11-12 i2c files added
2012-11-12 added template for RCT lib
2012-11-13 time from DS1338 successfully receives
2012-11-13 rtc sync with GPS done
2012-11-13 sending system time works
2012-11-14 SD logger written but not tested
2012-11-15 log writing works and tested
2012-11-16 initial ui commit
2012-11-19 added sources for xmodem protocol
2012-11-21 modem connection work
2012-11-21 added wrapper for writing to UDP socket
2012-11-21 added personal linker script
2012-11-21 updated generator script
2012-11-22 traffic shaper written. Need test.
2012-11-22 sending data over UDP works
2012-11-22 added message for long text
2012-11-22 UI works (leds and buttons)
2012-11-22 deleted unneded fields from sensors structures
2012-11-22 added more elegant resource usage show script
2012-11-23 reset pin for modem works
2012-11-23 parameters code integrated but not checked
2012-11-23 updated eeprom abstraction code
2012-11-24 remote parameter setting done and tested
2012-11-25 heartbeats from QGC successfully receives
2012-11-25 reduced stack for modem thread
2012-11-25 increased reset time for modem
2012-11-26 connection code with other divecis works
2012-11-26 face updated to new mavgen version
2012-11-26 Face. Changed port number for QGC from 14550 to 14554 to avoid conflicts with networkly connected QGC
2012-11-26 Fixed include of mavlink headers.
    Now extended messages handled correctly.
2012-11-27 added new messages to mavlink protocol
2012-11-27 GPS. Coordinates validity now checks using RMC package
2012-11-27 messaging improvements
2012-11-27 CPU loading code ready
2012-11-27 fully functional link with dysplay module
2012-11-27 cleaned gps code
2012-11-27 added fixe for eclipse indexer
2012-11-27 added draft code of CLI
2012-11-28 CLI works
2012-11-28 modem CLI works
2012-11-28 added help for modem cli
2012-11-28 loading connection settings from EEPROM to modem works
2012-11-28 added selftest command for CLI showing heartbeats from components
2012-11-28 removed snprintf() from uname command
2012-11-28 updated TODO
2012-11-29 selftesing applet works
2012-11-29 fixed bug with terminatin NULL
2012-11-29 added AGPS tester
2012-11-29 chat test added
2012-11-29 reduced I2C frequency to allow normal EEPROM functionality
2012-11-29 cosmetical fix in flash loader program
2012-11-29 mpiovd protocol renamed to oblique
2012-11-30 logger code reworked but not tested
2012-12-01 saved working unpackers
2012-12-01 code ready but not tested
2012-12-01 requesting count of packeages works
2012-12-02 sending data via rs-232 works but for UDP needs one package for one datagram
2012-12-02 data retrieving done
2012-12-03 retrieving data to CSV works
2012-12-03 data channel does not block now during acquiring storage via modem
2012-12-03 from circus progs deleted unused modules imports
2012-12-03 added ignore for acquired csv
2012-12-03 fixed some potential problems
2012-12-03 added restarting to modem code
2012-12-03 time correction written but needs to be checked
2012-12-04 exti works
2012-12-04 increased I2C speed after changing pull up resistors
2012-12-04 exti from PPS works
2012-12-04 smooth time syncing with GPS now works
2012-12-04 added CLI for storage
2012-12-05 cross works
2012-12-05 blinker timings tunung via parameters work
2012-12-05 analog00 field in mpiovd sensors packet renamed to voltage_battery
2012-12-05 Added ability to set time from CLI
2012-12-05 formatting improvements
2012-12-05 added switch to disable all DBG checks
2012-12-05 added check to modem cross applet
2012-12-05 message formatting improvements
2012-12-05 deleted unneded xmodem files
2012-12-05 storage voiding works
2012-12-05 storage wiping done
2012-12-06 added PIN passing to modem
2012-12-06 GSM reconnection works
2012-12-06 fixed RAM size in linker script
2012-12-07 cleared message definitions
2012-12-09 in addition to CGREG added CREG for modems register only in GPS network
2012-12-09 added package with rssi field from standard mavlink bulk
2012-12-10 deleted finished todo
2012-12-12 added display manager
2012-12-13 gps fix type corrected to conform with mavlink protocol
2012-12-13 added gui for DM
2012-12-13 rename
2012-12-13 added new gui for DM
2012-12-13 cleaned generated files
2012-12-13 compiled DM added to ignore
2012-12-15 added thread sending heartbeats in chat application
2012-12-15 added command for update some module firmware using single copy-paste operation
2012-12-15 added normal error handling and threading for chat.py application
2012-12-16 added icons for kamerton gui
2012-12-16 added test application
2012-12-17 added unicode support to matrix gui
2012-12-17 added config support to tester application
2012-12-17 matrixgui now uses config
2012-12-17 migrate to qt subproject layout
2012-12-17 renamed dm to telemetry
2012-12-17 telemetry application now use shared serial port lib
2012-12-19 icons splitted to separate files
2012-12-19 added sample of shitty color
2012-12-19 added make based converter from svg to png
2012-12-19 added color changing using config
2012-12-19 deleted unused code from matrixgui
2012-12-19 deleted autogenerated files
2012-12-21 reverted agps receiving from control center
2012-12-21 fixed agps demo
2012-12-21 added demo for route error indicating
2013-01-05 deleted TODO for firmware as outdated
2013-01-05 switched off ccache in Makefiles
2013-02-19 deleted trash from bnap dir
